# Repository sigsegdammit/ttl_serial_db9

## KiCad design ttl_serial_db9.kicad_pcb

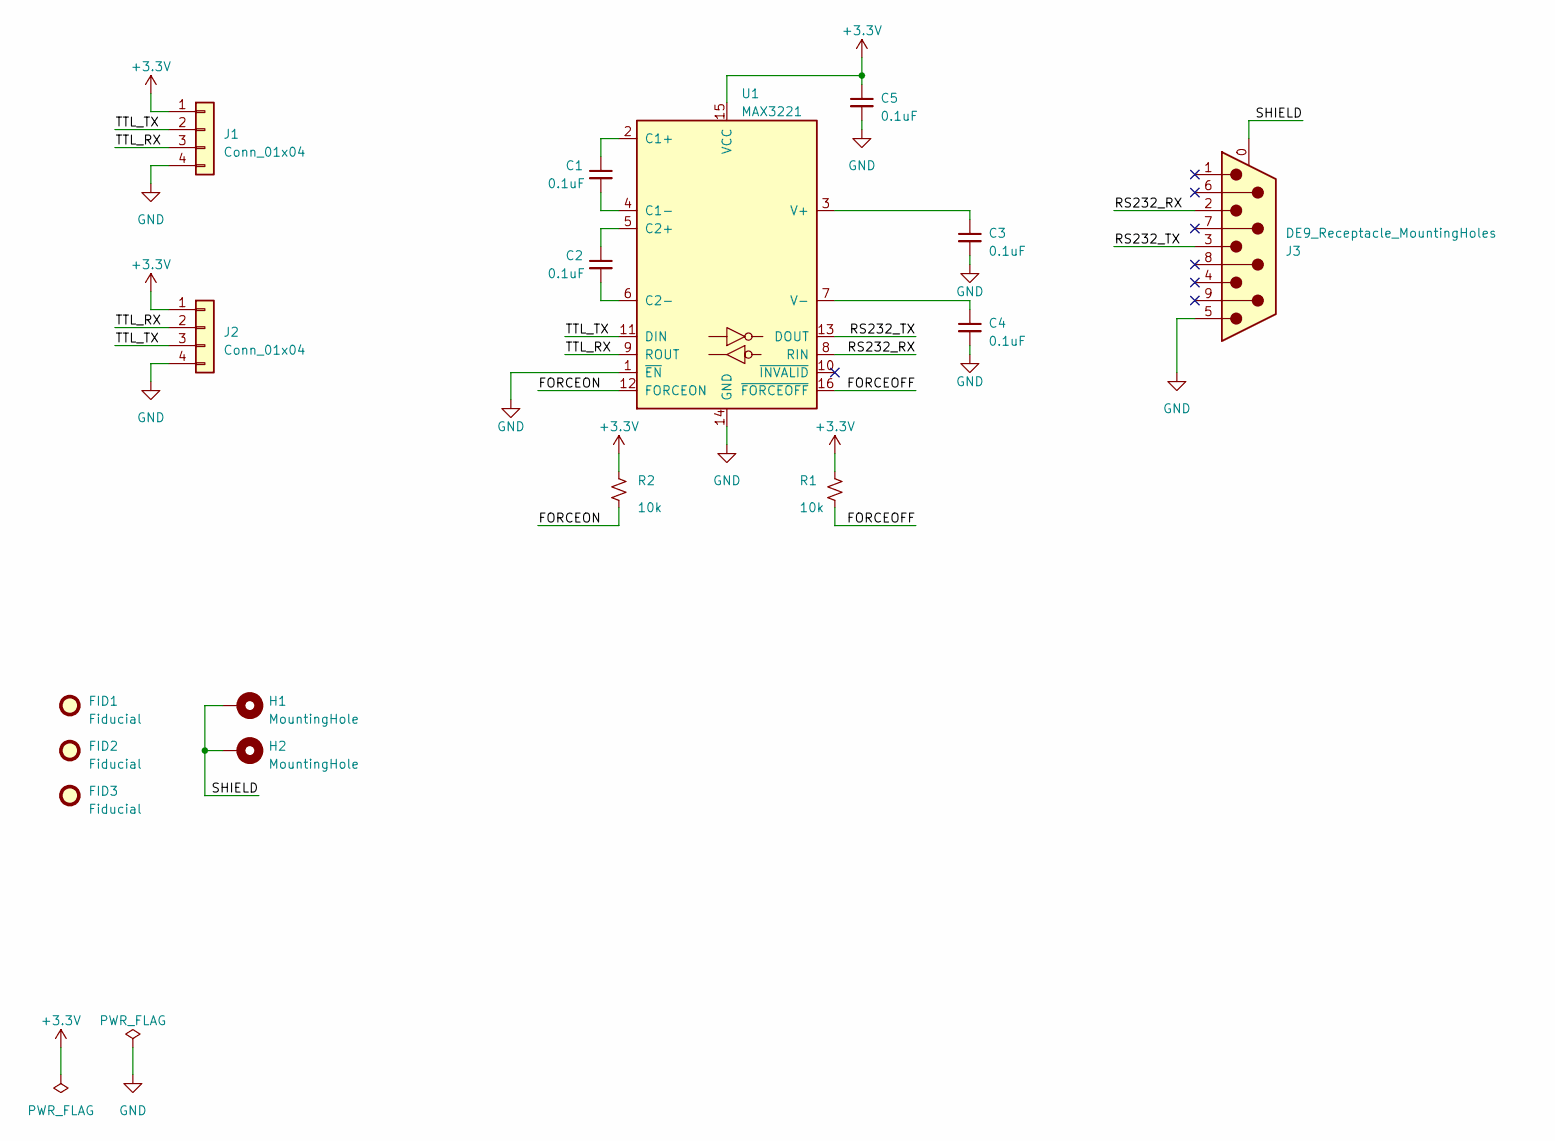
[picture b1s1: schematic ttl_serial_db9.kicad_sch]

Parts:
C1, C2, C3, C4, C5: 0.1uF; C_0603_1608Metric; LCSC C14663
FID1, FID2, FID3: Fiducial; fiducial_jlcpcb_smt
H1, H2: MountingHole; MountingHole_3.2mm_M3_Pad
J1, J2: Conn_01x04; PinHeader_1x04_P2.54mm_Horizontal; Mouser 649-1012937990403BLF
J3: DE9_Receptacle_MountingHoles; DSUB-9_Male_Horizontal_P2.77x2.84mm_EdgePinOffset7.70mm_Hou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; Mouser 636-182-009-213R561
R1, R2: 10k; R_0603_1608Metric; LCSC C25804
U1: MAX3221; TSSOP-16_4.4x5mm_P0.65mm; LCSC C44383

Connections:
+3.3V: C5.1, J1.1, J2.1, R1.1, R2.1, U1.15 (VCC)
/FORCEOFF: R1.2, U1.16 (~FORCEOFF)
/FORCEON: R2.2, U1.12 (FORCEON)
/RS232_RX: J3.2, U1.8 (RIN)
/RS232_TX: J3.3, U1.13 (DOUT)
/SHIELD: H1.1, H2.1, J3.0 (PAD)
/TTL_RX: J1.3, J2.2, U1.9 (ROUT)
/TTL_TX: J1.2, J2.3, U1.11 (DIN)
GND: C3.2, C4.2, C5.2, J1.4, J2.4, J3.5, U1.1 (~EN), U1.14 (GND)
unnamed: C1.1, U1.2 (C1+)
unnamed: C1.2, U1.4 (C1-)
unnamed: C2.1, U1.5 (C2+)
unnamed: C2.2, U1.6 (C2-)
unnamed: C3.1, U1.3 (V+)
unnamed: C4.1, U1.7 (V-)

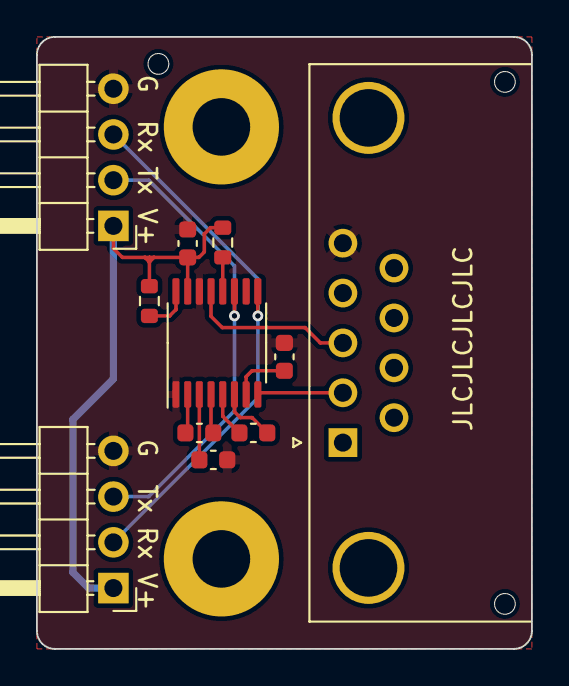
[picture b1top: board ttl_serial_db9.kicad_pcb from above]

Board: 2 copper layers, 27.5 x 34.0 mm, 16 parts (0 on the bottom side), 15 nets.

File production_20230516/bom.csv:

Designator,Footprint,Quantity,Value,LCSC Part #
"C1, C2, C3, C4, C5",0603,5,0.1uF,C14663
"FID1, FID2, FID3",fiducial_jlcpcb_smt,3,Fiducial,
"H1, H2",MountingHole_3.2mm_M3_Pad,2,MountingHole,
"J1, J2",PinHeader_1x04_P2.54mm_Horizontal,2,Conn_01x04,
J3,DSUB-9_Male_Horizontal_P2.77x2.84mm_EdgePinOffset7.70mm_Housed_MountingHolesOffset9.12mm,1,DE9_Receptacle_MountingHoles,
"R1, R2",0603,2,10k,C25804
U1,TSSOP-16_4.4x5mm_P0.65mm,1,MAX3221,C44383

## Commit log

2023-05-16 TTL with reversed tx/rx to rs-232 DB9
2023-05-16 Production files as sent to fab
